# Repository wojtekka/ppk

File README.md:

Palm™ Portable Keyboard USB adapter
===================================

Based on CH552 Macropad mini by Stefan Wagner (https://github.com/wagiminator/CH552-Macropad-mini). Headers from the original code:

    // ===================================================================================
    // Project:   MacroPad Mini for CH551, CH552 and CH554
    // Version:   v1.3
    // Year:      2023
    // Author:    Stefan Wagner
    // Github:    https://github.com/wagiminator
    // EasyEDA:   https://easyeda.com/wagiminator
    // License:   http://creativecommons.org/licenses/by-sa/3.0/
    // ===================================================================================

    # Project:   chprog - Programming Tool for CH55x Microcontrollers
    # Version:   v1.1
    # Year:      2022
    # Author:    Stefan Wagner
    # Github:    https://github.com/wagiminator
    # License:   MIT License

Based on Gist by Mightypork (https://gist.github.com/MightyPork/6da26e382a7ad91b5496ee55fdc73db2)

Key mapping compatible with https://github.com/pymo/ppk_bluetooth/

Hardware design released into public domain.

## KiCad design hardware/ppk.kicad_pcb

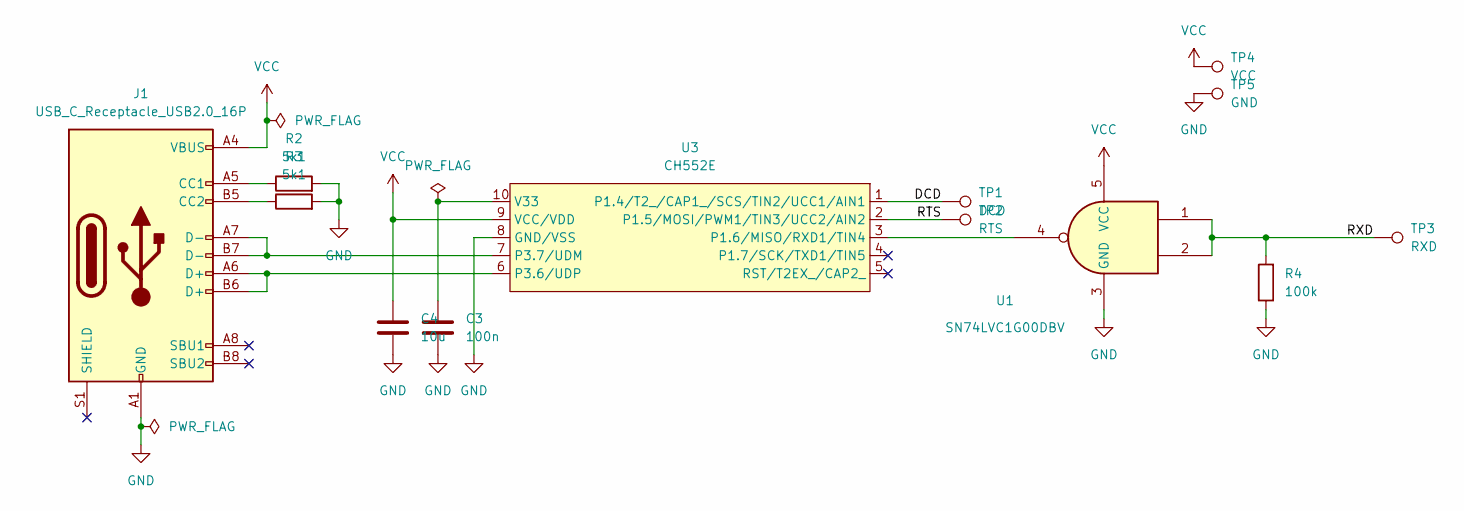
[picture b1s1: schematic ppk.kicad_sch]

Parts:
C3: 100n; C_0805_2012Metric
C4: 10u; C_0805_2012Metric
J1: USB_C_Receptacle_USB2.0_16P; USB_C_Receptacle_GCT_USB4110
R2, R3: 5k1; R_0805_2012Metric
R4: 100k; R_0805_2012Metric
TP1: DCD; TestPoint_Pad_1.5x1.5mm
TP2: RTS; TestPoint_Pad_1.5x1.5mm
TP3: RXD; TestPoint_Pad_1.5x1.5mm
TP4: VCC; TestPoint_Pad_1.5x1.5mm
TP5: GND; TestPoint_Pad_1.5x1.5mm
U1: SN74LVC1G00DBV; SOT-23-5
U3: CH552E; MSOP-10_3x3mm_P0.5mm

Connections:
/DCD: TP1.1, U3.1 (P1.4/T2_/CAP1_/SCS/TIN2/UCC1/AIN1)
/RTS: TP2.1, U3.2 (P1.5/MOSI/PWM1/TIN3/UCC2/AIN2)
/RXD: R4.2, TP3.1, U1.1, U1.2
GND: C3.2, C4.2, J1.A1 (GND), J1.A12 (GND), J1.B1 (GND), J1.B12 (GND), R2.2, R3.2, R4.1, TP5.1, U1.3 (GND), U3.8 (GND/VSS)
unnamed: J1.A5 (CC1), R2.1
unnamed: J1.B5 (CC2), R3.1
unnamed: U1.4, U3.3 (P1.6/MISO/RXD1/TIN4)
unnamed: J1.A6 (D+), J1.B6 (D+), U3.6 (P3.6/UDP)
unnamed: J1.A7 (D-), J1.B7 (D-), U3.7 (P3.7/UDM)
unnamed: C3.1, U3.10 (V33)
VCC: C4.1, J1.A4 (VBUS), J1.A9 (VBUS), J1.B4 (VBUS), J1.B9 (VBUS), TP4.1, U1.5 (VCC), U3.9 (VCC/VDD)

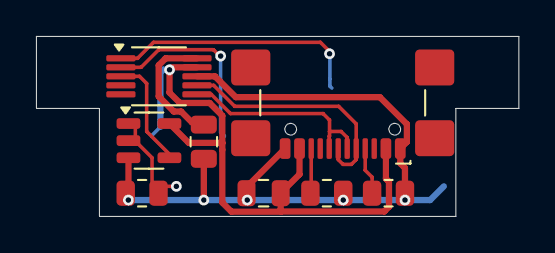
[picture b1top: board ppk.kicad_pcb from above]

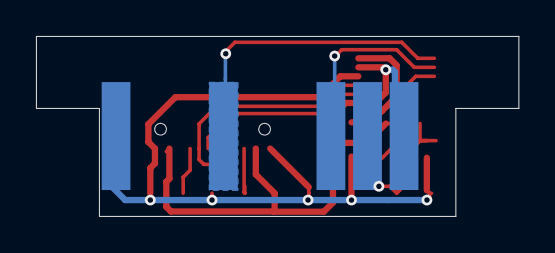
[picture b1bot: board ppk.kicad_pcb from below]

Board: 2 copper layers, 26.8 x 10.0 mm, 13 parts (5 on the bottom side), 11 nets.

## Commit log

2024-10-11 Import to Git
2024-10-11 Schematic
2024-11-14 Use assigned USB pid/vid
2025-09-16 Hardware design in KiCad
